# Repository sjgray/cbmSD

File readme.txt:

cbmSD family of SD Card Drives for Commodore Computers with IEEE
================================================================

The goal of this project is to create free open-source disk drive
solutions that are easy to build using all thru-hole parts plus
the use of a common inexpensive SD card module.

There are several variations depending on your usage:

1) cbmSD  (In development)
           A full solution providing both IEEE and IEC ports.
           For use on PET/CBM and most Commodore 8-bit machines.
           Direct-plug for IEEE but can connect to IEC devices
           with standard IEC cable.

2) cbmSD-mini
           Direct-plug solutions for PET/CBM machines with IEEE.
           With IEEE pass-thru.

3) cbmSD-xd
           Proprietary cable solution for PET/CBM machines.
           Several Pass-thru boards connect to back of computer, with ribbon cable to SD card board.
           No expensive IEEE cable required.

You will need a simple cassette port power plug or you can
power it with a standard 5V adapter with barrel jack.

Project Page
------------

http://www.cbmsteve.ca/cbmsd/index.html

Status
------

DEVICE     VER   DATE       STATUS

cbmSD      -     -          In development. Requires firmware changes
cbmSD-mini 1.2   2024-02-21 Working
cbmSD-mini 1.2v  2024-07-30 Working. Vertical mounting option.
cbmSD-xd   1.0   2024-11-18 Working. Requires cbmSD-pass board.
pass-e2e   1.0   2024-11-18 Working. Edge-2-Edge
pass-e2c   1.0   1014-11-22 Working. Edge-2-Centronics female
pass-c2e   1.0   2025-12-01 Untested. Centronics-2-Edge

Steve
2025-12-14

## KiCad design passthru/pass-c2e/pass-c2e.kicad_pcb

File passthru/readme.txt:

cbmSD-pass - Pass-thru board for cbmSD-xd
=========================================

**NEW** Webpage: http://cbmsteve.ca/cbmsd/index.html

These pass-thru boards plug into the back of the PET/CBM and
connects to power (via cassette port or power adapter).
The "XD" connector combines the power and IEEE signals into one
proprietary pinout for convenient connection to the cbmSD-xd
board using a simple 20-pin ribbon cable. Note: That the IEEE
standard is a 24-pin connector. The GROUND pins have been
consolidated and 5V pins have been added.

You will need a simple cassette port power plug or you can
power it with a standard 5V adapter with barrel jack.

There are three versions available:

1) "E2E" - Edge-2-Edge. Edge connector output. Horizontal or Vertical mount options.
2) "E2C" - Edge-2-Centronics. Centronics female connector as used on devices.
3) "C2E" - Centronics-2-Edge. For SK machines.

Features
--------

- Proprietary 20-pin "cbmSD" header (IEEE + Power).
- Barrel Jack for 5V power.
- Power LED.
- Passthru connector to additional devices.

Status
------

2024-11-10 E2E V1.0 - Verified working as intended.
2024-11-22 E2C V1.0 - Verified working as intended.
2025-12-01 C2E V1.0 - Untested.

Steve
2025-12-14

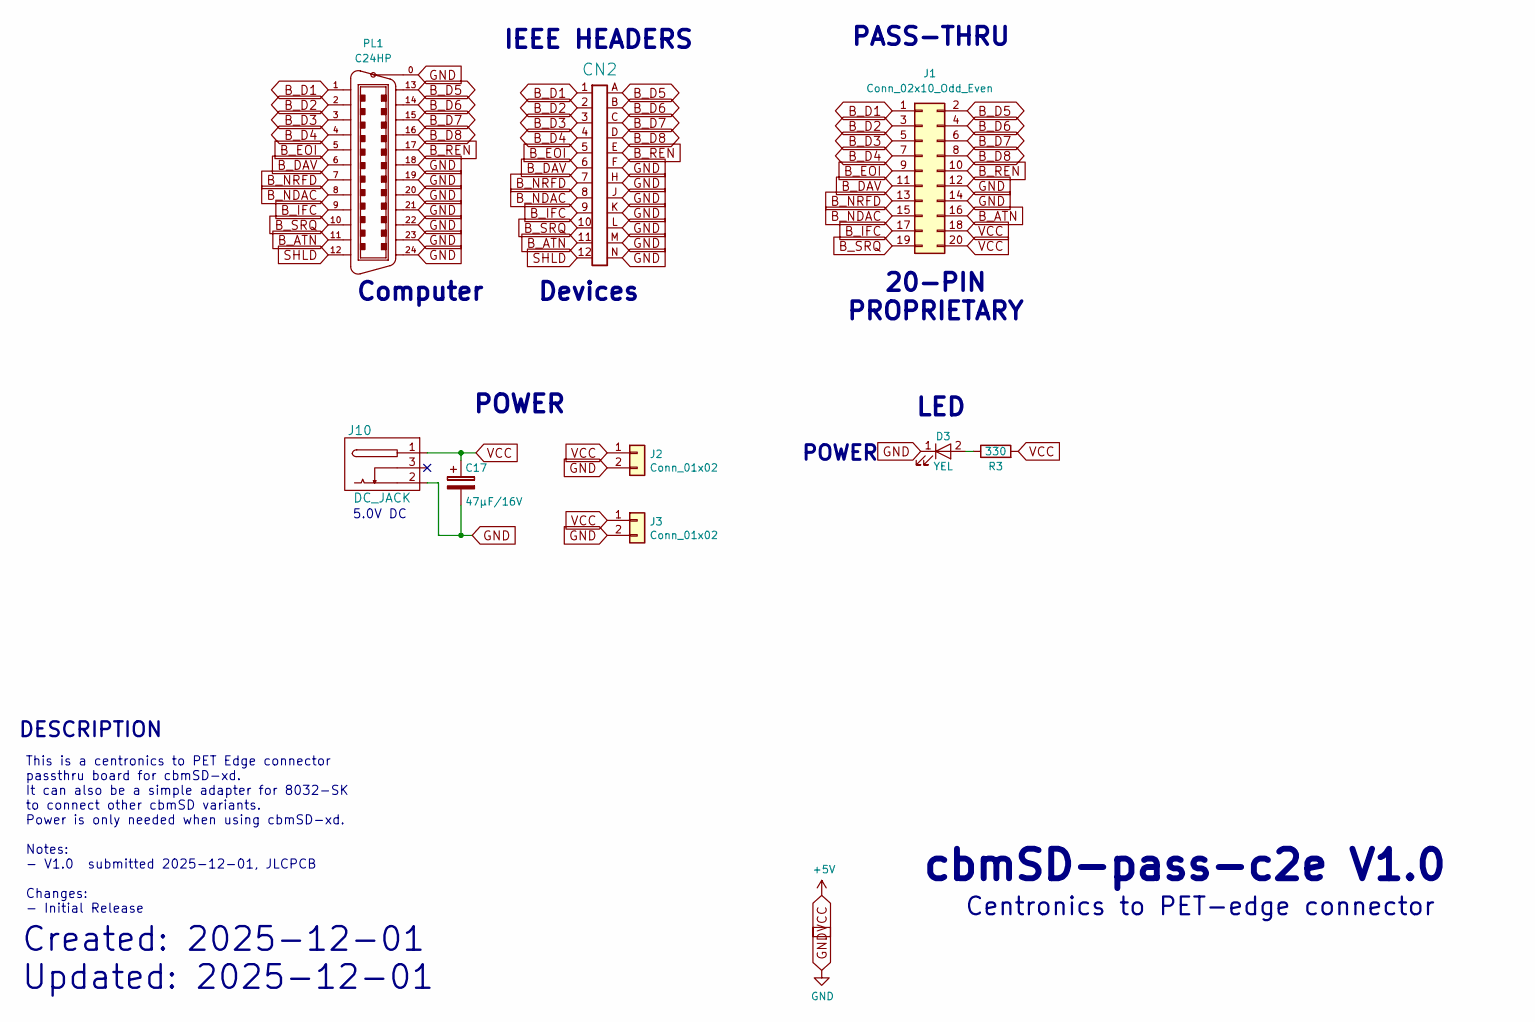
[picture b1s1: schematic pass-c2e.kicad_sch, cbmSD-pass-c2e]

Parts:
C17: 47µF/16V; CP_Radial_D4.0mm_P1.50mm
CN2: EDGE_CON_02x12; EDGE_CON_24P
D3: YEL; LED_D3.0mm_Clear
J1: Conn_02x10_Odd_Even; PinHeader_2x10_P2.54mm_Vertical
J2, J3: Conn_01x02; PinHeader_1x02_P2.54mm_Vertical
J10: DC_JACK; BarrelJack_Horizontal
PL1: C24HP; con-amp-champ-24HP
R3: 330; R_Axial_DIN0207_L6.3mm_D2.5mm_P10.16mm_Horizontal

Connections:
B_ATN: CN2.11, J1.16, PL1.11
B_D1: CN2.1, J1.1, PL1.1
B_D2: CN2.2, J1.3, PL1.2
B_D3: CN2.3, J1.5, PL1.3
B_D4: CN2.4, J1.7, PL1.4
B_D5: CN2.A, J1.2, PL1.13
B_D6: CN2.B, J1.4, PL1.14
B_D7: CN2.C, J1.6, PL1.15
B_D8: CN2.D, J1.8, PL1.16
B_DAV: CN2.6, J1.11, PL1.6
B_EOI: CN2.5, J1.9, PL1.5
B_IFC: CN2.9, J1.17, PL1.9
B_NDAC: CN2.8, J1.15, PL1.8
B_NRFD: CN2.7, J1.13, PL1.7
B_REN: CN2.E, J1.10, PL1.17
B_SRQ: CN2.10, J1.19, PL1.10
GND: C17.2, CN2.F, CN2.H, CN2.J, CN2.K, CN2.L, CN2.M, CN2.N, D3.1 (K), J1.12, J1.14, J2.2, J3.2, J10.2, PL1.0, PL1.18, PL1.19, PL1.20, PL1.21, PL1.22, PL1.23, PL1.24
unnamed: D3.2 (A), R3.1
SHLD: CN2.12, PL1.12
VCC: C17.1, J1.18, J1.20, J2.1, J3.1, J10.1, R3.2

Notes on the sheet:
5.0V DC
Computer
Centronics to PET-edge connector
This is a centronics to PET Edge connector passthru board for cbmSD-xd. It can also be a simple adapter for 8032-SK to connect other cbmSD variants. Power is only needed when using cbmSD-xd. Notes: - V1.0 submitted 2025-12-01, JLCPCB Changes: - Initial Release
DESCRIPTION
Devices
cbmSD-pass-c2e V1.0
PASS-THRU
IEEE HEADERS
POWER
20-PIN PROPRIETARY
LED
Created: 2025-12-01 Updated: 2025-12-01

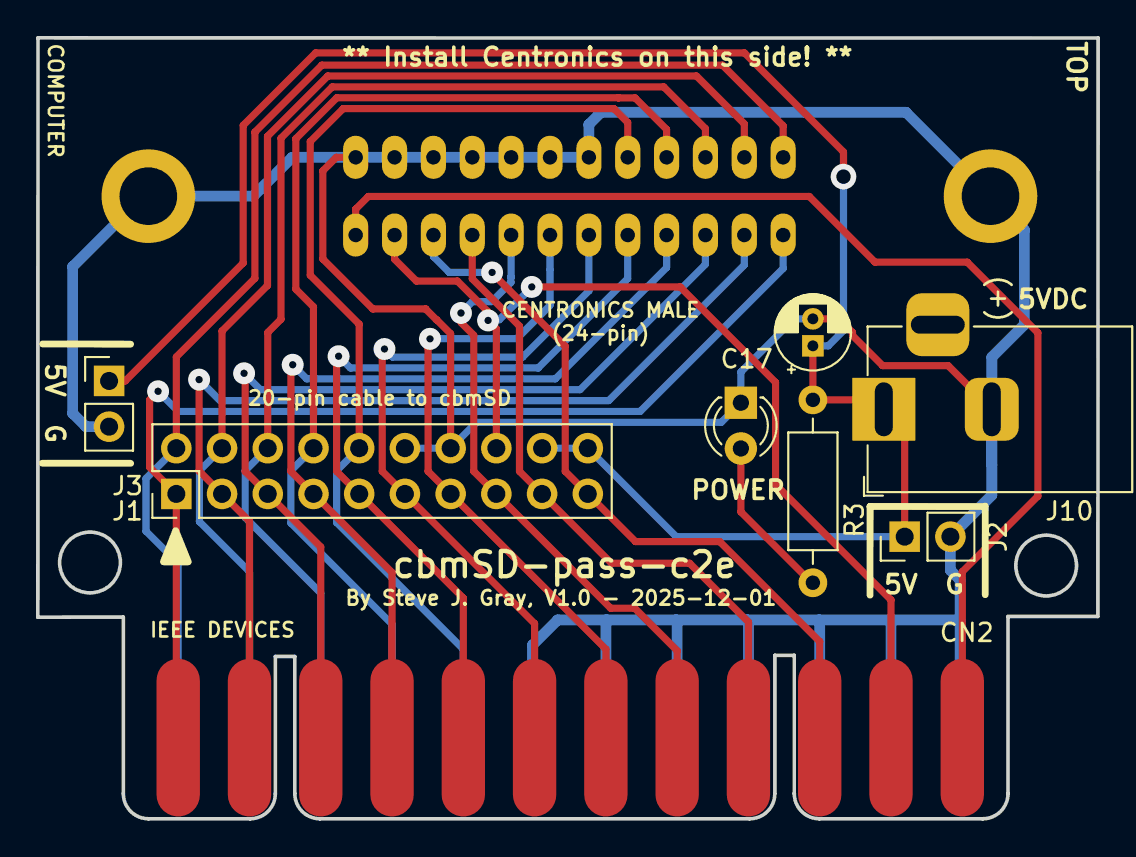
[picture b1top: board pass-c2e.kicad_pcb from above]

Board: 2 copper layers, 58.9 x 43.4 mm, 9 parts (1 on the bottom side), 20 nets.

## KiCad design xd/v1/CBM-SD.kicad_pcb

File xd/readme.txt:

cbmSD-xd - SD Card Drive for Commodore Computers with IEEE
==========================================================

**NEW** Webpage: http://cbmsteve.ca/cbmsd/index.html

The goal of this project is to create a free open-source
disk drive solution that is easy to build using all
thru-hole parts plus the use of a common inexpensive SD
card module.

This device is based on the petSD+ v2.4 from Nils Eilers.

This is a variant of cbmSD-mini. The "XD" stands for
eXternal Drive (or eXperimental Device as I am not sure
what the ultimate form this might be).

This version comes in two parts:

1) IEEE pass-thru and "cbmSD" connector.
2) cbmSD-xd board

The pass-thru plugs into the back of the PET/CBM and connects
to power (via cassette port or power adapter). The "XD"
connector combines the power and IEEE signals into one
proprietary pinout for convenient connection to the cbmSD-xd
board using a simple 20-pin ribbon cable. Note: That the IEEE
standard is a 24-pin connector. The GROUND pins have been
consolidated and 5V pins have been added.

You will need a simple cassette port power plug or you can
power it with a standard 5V adapter with barrel jack.

Features
--------

- Requires cbmSD-pass board (there are 2 variations)
- Proprietary 20-pin IEEE/Power connector
- Power, Busy and Error lights
- SD module is mounted directly to pcb so it does not mount
  overtop any components
- Reset switch.
- Mounting holes for future 3D case.

Status
------

 V1.0: First release. Verified working as intended.

Steve
2025-01-13

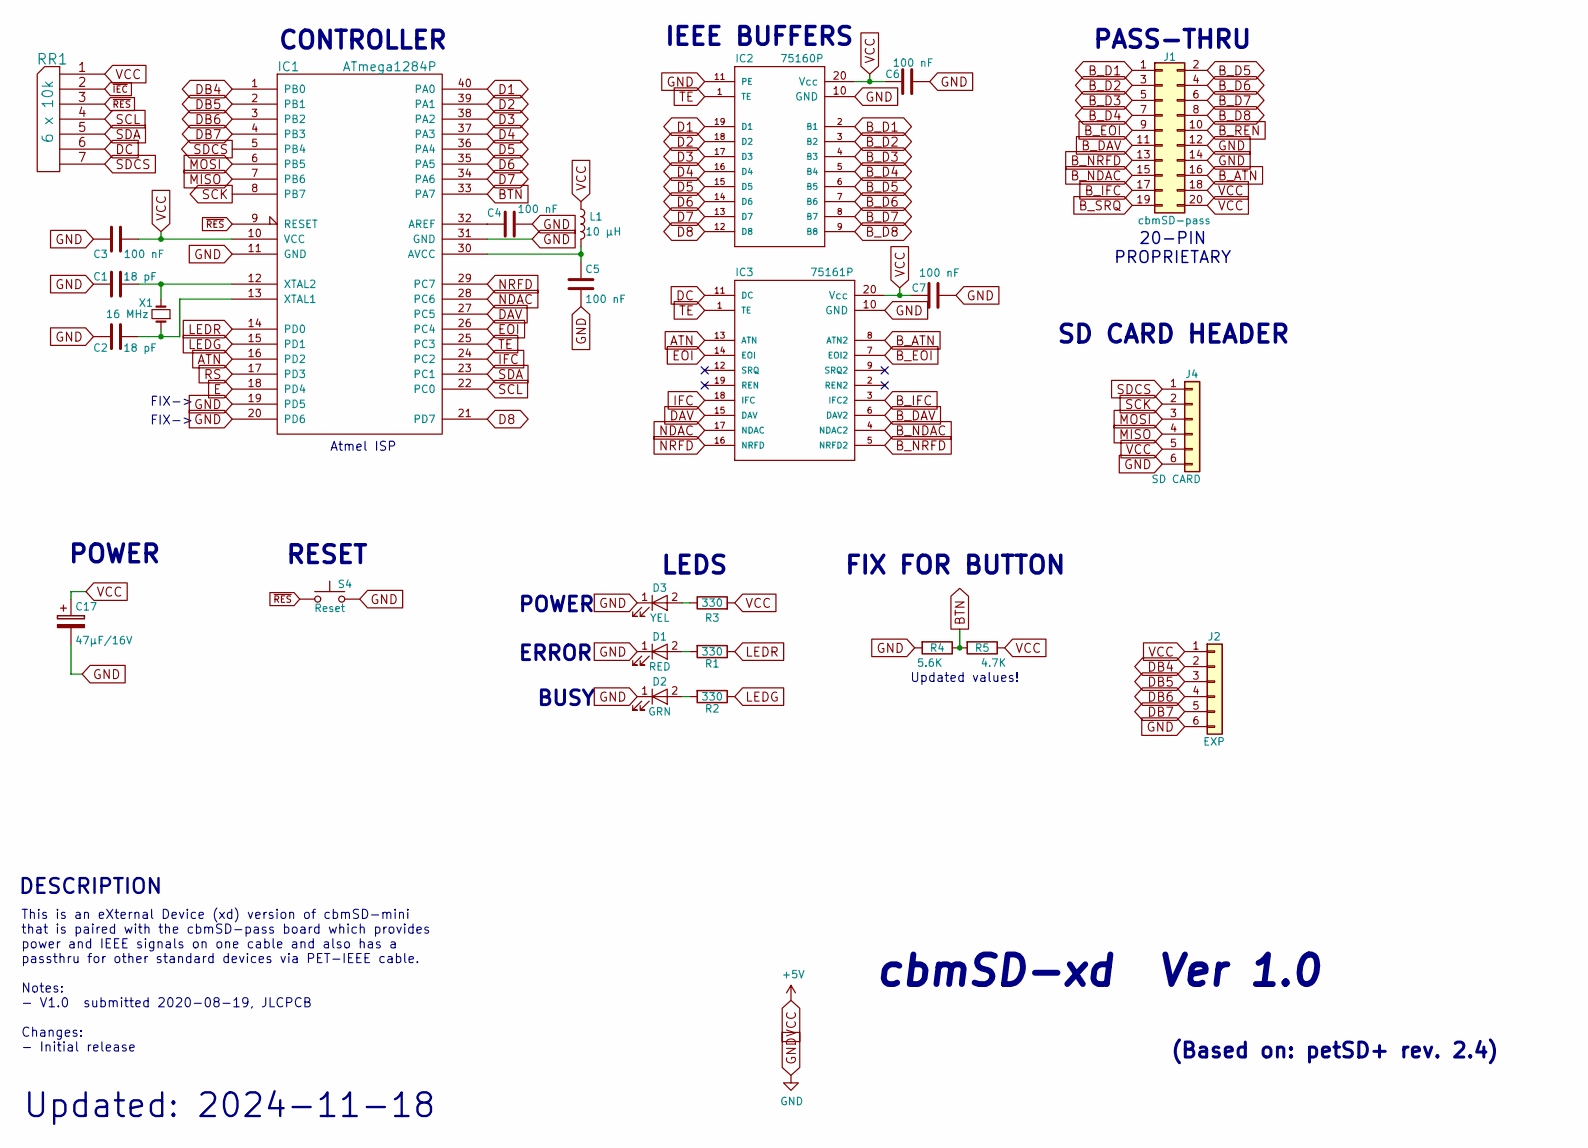
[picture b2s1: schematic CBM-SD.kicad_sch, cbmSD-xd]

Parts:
C1, C2: 18 pF; C_Disc_D3.8mm_W2.6mm_P2.50mm
C3, C4, C5, C6, C7: 100 nF; C_Disc_D3.8mm_W2.6mm_P2.50mm
C17: 47µF/16V; CP_Radial_D6.3mm_P2.50mm
D1: RED; LED_D3.0mm_Clear
D2: GRN; LED_D3.0mm_Clear
D3: YEL; LED_D3.0mm_Clear
IC1: ATmega1284P; DIP-40_W15.24mm
IC2: 75160P; DIP-20_W7.62mm
IC3: 75161P; DIP-20_W7.62mm
J1: cbmSD-pass; PinHeader_2x10_P2.54mm_Vertical
J2: EXP; PinHeader_1x06_P2.54mm_Vertical
J4: SD CARD; PinHeader_1x06_P2.54mm_Vertical
L1: 10 µH; L_Axial_L7.0mm_D3.3mm_P10.16mm_Horizontal_Fastron_MICC
R1, R2, R3: 330; R_Axial_DIN0207_L6.3mm_D2.5mm_P10.16mm_Horizontal
R4: 5.6K; R_Axial_DIN0207_L6.3mm_D2.5mm_P10.16mm_Horizontal
R5: 4.7K; R_Axial_DIN0207_L6.3mm_D2.5mm_P10.16mm_Horizontal
RR1: 6 x 10k; R_Array_SIP7
S4: Reset; SW_Tactile_SKHH_Angled
X1: 16 MHz; Crystal_HC49-4H_Vertical

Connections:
ATN: IC1.16 (PD2), IC3.13 (ATN)
BTN: IC1.33 (PA7), R4.1, R5.2
B_ATN: IC3.8 (ATN2), J1.16
B_D1: IC2.2 (B1), J1.1
B_D2: IC2.3 (B2), J1.3
B_D3: IC2.4 (B3), J1.5
B_D4: IC2.5 (B4), J1.7
B_D5: IC2.6 (B5), J1.2
B_D6: IC2.7 (B6), J1.4
B_D7: IC2.8 (B7), J1.6
B_D8: IC2.9 (B8), J1.8
B_DAV: IC3.6 (DAV2), J1.11
B_EOI: IC3.7 (EOI2), J1.9
B_IFC: IC3.3 (IFC2), J1.17
B_NDAC: IC3.4 (NDAC2), J1.15
B_NRFD: IC3.5 (NRFD2), J1.13
B_REN: J1.10
B_SRQ: J1.19
D1: IC1.40 (PA0), IC2.19 (D1)
D2: IC1.39 (PA1), IC2.18 (D2)
D3: IC1.38 (PA2), IC2.17 (D3)
D4: IC1.37 (PA3), IC2.16 (D4)
D5: IC1.36 (PA4), IC2.15 (D5)
D6: IC1.35 (PA5), IC2.14 (D6)
D7: IC1.34 (PA6), IC2.13 (D7)
D8: IC1.21 (PD7), IC2.12 (D8)
DAV: IC1.27 (PC5), IC3.15 (DAV)
DB4: IC1.1 (PB0), J2.2
DB5: IC1.2 (PB1), J2.3
DB6: IC1.3 (PB2), J2.4
DB7: IC1.4 (PB3), J2.5
DC: IC3.11 (DC), RR1.6
E: IC1.18 (PD4)
EOI: IC1.26 (PC4), IC3.14 (EOI)
GND: C1.1, C2.1, C3.1, C4.2, C5.2, C6.1, C7.1, C17.2, D1.1 (K), D2.1 (K), D3.1 (K), IC1.11 (GND), IC1.19 (PD5), IC1.20 (PD6), IC1.31 (GND), IC2.10 (GND), IC2.11 (PE), IC3.10 (GND), J1.12, J1.14, J2.6, J4.6, R4.2, S4.2
IFC: IC1.24 (PC2), IC3.18 (IFC)
LEDG: IC1.15 (PD1), R2.1
LEDR: IC1.14 (PD0), R1.1
MISO: IC1.7 (PB6), J4.4
MOSI: IC1.6 (PB5), J4.3
NDAC: IC1.28 (PC6), IC3.17 (NDAC)
NRFD: IC1.29 (PC7), IC3.16 (NRFD)
unnamed: D1.2 (A), R1.2
unnamed: D2.2 (A), R2.2
unnamed: D3.2 (A), R3.1
unnamed: C4.1, IC1.32 (AREF)
unnamed: C5.1, IC1.30 (AVCC), L1.2
unnamed: C2.2, IC1.13 (XTAL1), X1.1
unnamed: C1.2, IC1.12 (XTAL2), X1.2
RS: IC1.17 (PD3)
SCK: IC1.8 (PB7), J4.2
SCL: IC1.22 (PC0), RR1.4
SDA: IC1.23 (PC1), RR1.5
SDCS: IC1.5 (PB4), J4.1, RR1.7
TE: IC1.25 (PC3), IC2.1 (TE), IC3.1 (TE)
VCC: C3.2, C6.2, C7.2, C17.1, IC1.10 (VCC), IC2.20 (Vcc), IC3.20 (Vcc), J1.18, J1.20, J2.1, J4.5, L1.1, R3.2, R5.1, RR1.1 (COM)
~IEC: RR1.2
~RES: IC1.9 (RESET), RR1.3, S4.1

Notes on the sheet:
Updated values!
BUSY
This is an eXternal Device (xd) version of cbmSD-mini that is paired with the cbmSD-pass board which provides power and IEEE signals on one cable and also has a passthru for other standard devices via PET-IEEE cable. Notes: - V1.0 submitted 2020-08-19, JLCPCB Changes: - Initial release
PASS-THRU
20-PIN PROPRIETARY
Atmel ISP
DESCRIPTION
FIX FOR BUTTON
SD CARD HEADER
cbmSD-xd Ver 1.0
CONTROLLER
(Based on: petSD+ rev. 2.4)
FIX->
POWER
RESET
LEDS
ERROR
Updated: 2024-11-18
IEEE BUFFERS

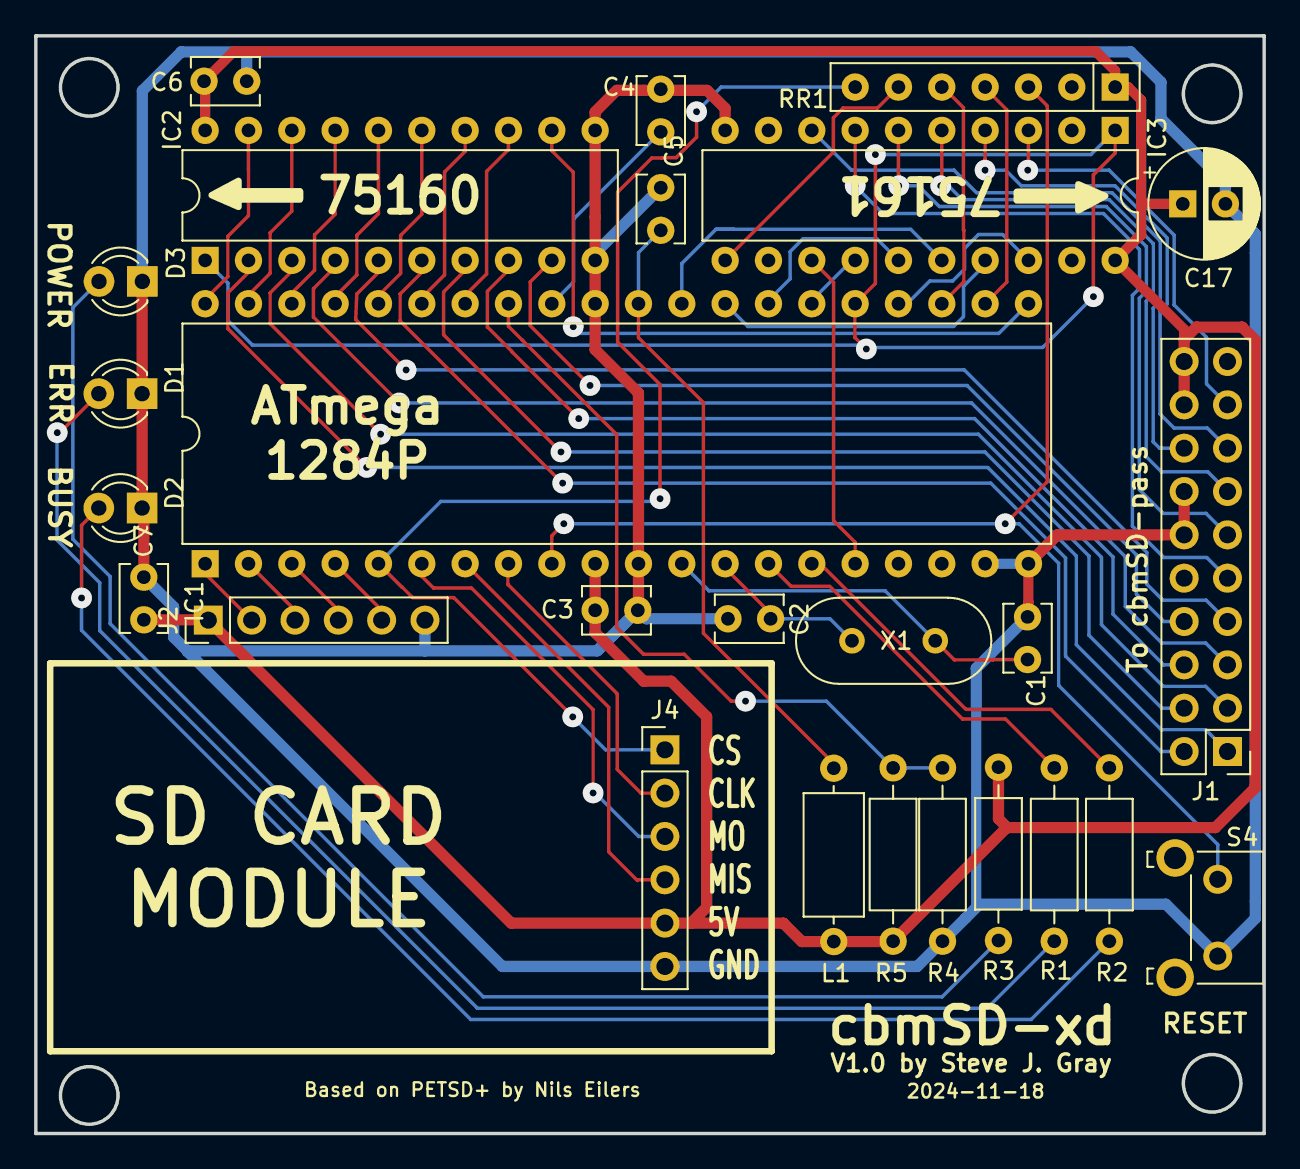
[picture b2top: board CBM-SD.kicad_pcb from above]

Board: 2 copper layers, 72.0 x 64.3 mm, 26 parts (0 on the bottom side), 53 nets.

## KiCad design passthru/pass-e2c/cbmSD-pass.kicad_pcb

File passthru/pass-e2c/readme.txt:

cbmSD-pass - IEEE passthru for remote cbmSD Drive
=================================================

**NEW** Webpage: http://cbmsteve.ca/cbmsd/index.html

The goal of this project is to create a free open-source
disk drive solution that is easy to build using all
thru-hole parts plus the use of a common inexpensive SD
card module.

This is an IEEE pass-thru and connection to remote
cbmSD device and to allow normal IEEE devices to be
chained to the PET computer.

Status
------

 V1.0: First cbmSD-pass board

Steve
2024-11-16

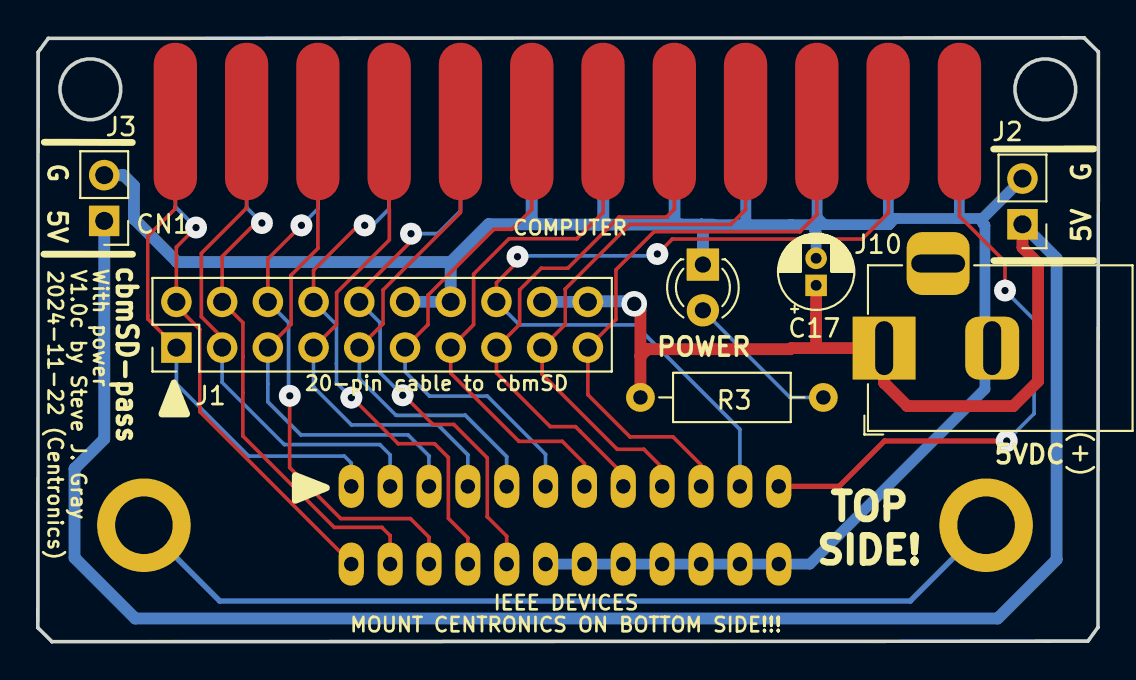
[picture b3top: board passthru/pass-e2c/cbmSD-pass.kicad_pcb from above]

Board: 2 copper layers, 58.9 x 33.5 mm, 9 parts (1 on the bottom side), 20 nets.

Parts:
C17: 47µF/16V; CP_Radial_D4.0mm_P1.50mm
CN1: EDGE_CON_02x12; EDGE_CON_24P
D3: YEL; LED_D3.0mm_Clear
J1: Conn_02x10_Odd_Even; PinHeader_2x10_P2.54mm_Vertical
J2, J3: Conn_01x02; PinHeader_1x02_P2.54mm_Vertical
J10: DC_JACK; BarrelJack_Horizontal
PL1: C24HP; con-amp-champ-24HP
R3: 330; R_Axial_DIN0207_L6.3mm_D2.5mm_P10.16mm_Horizontal

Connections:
B_ATN: CN1.11, J1.16, PL1.11
B_D1: CN1.1, J1.1, PL1.1
B_D2: CN1.2, J1.3, PL1.2
B_D3: CN1.3, J1.5, PL1.3
B_D4: CN1.4, J1.7, PL1.4
B_D5: CN1.A, J1.2, PL1.13
B_D6: CN1.B, J1.4, PL1.14
B_D7: CN1.C, J1.6, PL1.15
B_D8: CN1.D, J1.8, PL1.16
B_DAV: CN1.6, J1.11, PL1.6
B_EOI: CN1.5, J1.9, PL1.5
B_IFC: CN1.9, J1.17, PL1.9
B_NDAC: CN1.8, J1.15, PL1.8
B_NRFD: CN1.7, J1.13, PL1.7
B_REN: CN1.E, J1.10, PL1.17
B_SRQ: CN1.10, J1.19, PL1.10
GND: C17.2, CN1.F, CN1.H, CN1.J, CN1.K, CN1.L, CN1.M, CN1.N, D3.1 (K), J1.12, J1.14, J2.2, J3.2, J10.2, PL1.18, PL1.19, PL1.20, PL1.21, PL1.22, PL1.23, PL1.24
unnamed: D3.2 (A), R3.1
SHLD: CN1.12, PL1.12
VCC: C17.1, J1.18, J1.20, J2.1, J3.1, J10.1, R3.2

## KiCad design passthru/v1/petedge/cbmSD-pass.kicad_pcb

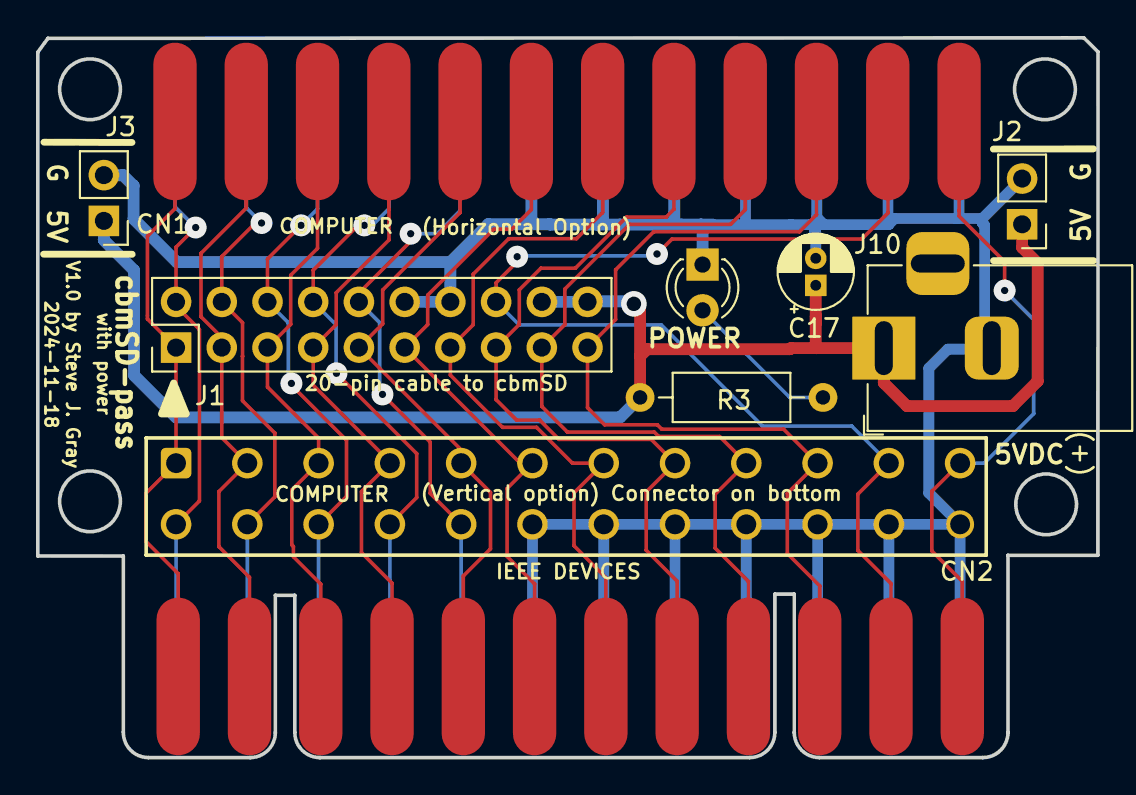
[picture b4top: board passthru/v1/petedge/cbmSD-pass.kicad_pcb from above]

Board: 2 copper layers, 58.9 x 40.0 mm, 10 parts (1 on the bottom side), 20 nets.

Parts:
C17: 47µF/16V; CP_Radial_D4.0mm_P1.50mm
CN1, CN2: EDGE_CON_02x12; EDGE_CON_24P
CN3: EDGE_CON_02x12; EDGE_02x12-VERTICAL_THT
D3: YEL; LED_D3.0mm_Clear
J1: Conn_02x10_Odd_Even; PinHeader_2x10_P2.54mm_Vertical
J2, J3: Conn_01x02; PinHeader_1x02_P2.54mm_Vertical
J10: DC_JACK; BarrelJack_Horizontal
R3: 330; R_Axial_DIN0207_L6.3mm_D2.5mm_P10.16mm_Horizontal

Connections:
B_ATN: CN1.11, CN2.11, CN3.11, J1.16
B_D1: CN1.1, CN2.1, CN3.1, J1.1
B_D2: CN1.2, CN2.2, CN3.2, J1.3
B_D3: CN1.3, CN2.3, CN3.3, J1.5
B_D4: CN1.4, CN2.4, CN3.4, J1.7
B_D5: CN1.A, CN2.A, CN3.A, J1.2
B_D6: CN1.B, CN2.B, CN3.B, J1.4
B_D7: CN1.C, CN2.C, CN3.C, J1.6
B_D8: CN1.D, CN2.D, CN3.D, J1.8
B_DAV: CN1.6, CN2.6, CN3.6, J1.11
B_EOI: CN1.5, CN2.5, CN3.5, J1.9
B_IFC: CN1.9, CN2.9, CN3.9, J1.17
B_NDAC: CN1.8, CN2.8, CN3.8, J1.15
B_NRFD: CN1.7, CN2.7, CN3.7, J1.13
B_REN: CN1.E, CN2.E, CN3.E, J1.10
B_SRQ: CN1.10, CN2.10, CN3.10, J1.19
GND: C17.2, CN1.F, CN1.H, CN1.J, CN1.K, CN1.L, CN1.M, CN1.N, CN2.F, CN2.H, CN2.J, CN2.K, CN2.L, CN2.M, CN2.N, CN3.F, CN3.H, CN3.J, CN3.K, CN3.L, CN3.M, CN3.N, D3.1 (K), J1.12, J1.14, J2.2, J3.2, J10.2
unnamed: D3.2 (A), R3.1
SHLD: CN1.12, CN2.12, CN3.12
VCC: C17.1, J1.18, J1.20, J2.1, J3.1, J10.1, R3.2

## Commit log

2025-01-13 Re-name and Re-Org. Add cbmSD-xd.
    Rename repository to "cbmSD" and Re-structure directories to reflect "family" of devices. Add cbmSD-xd v1.0 and cbmSD-pass V1.0 boards. Updated readme files for all.
2025-12-14 Add C2E passthru for SK machines
    Add C2E. Re-org folder names. Update readmes

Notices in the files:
xd/v1/CBM-SD.kicad_sch:
Schematic and PCB layout licensed under CC-BY-SA 4.0
